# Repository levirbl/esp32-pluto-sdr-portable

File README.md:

# Portable SDR — ESP32-S3 + Pluto SDR

A handheld radio from 70 MHz to 6 GHz: spectrum and waterfall (with integrated spectrum, traces and
fine RBW), audio (AM, FM, SSB and CW) with automatic noise reduction, recording, decoders (RDS, ADS-B,
AIS, APRS, radiosondes, VOR, FPV drones), hydrogen-line radio astronomy, satellite pass prediction with Doppler correction, an RF
oscilloscope and **amateur radio transmit** on 2 m and 70 cm (test tone, WAV file in NFM, USB or
LSB, CW identification and CW messages, tracking generator, replay of IQ recordings), plus a **Tools**
app (image viewer, text editor, RF and antenna calculators, stopwatch and timer, metronome, IQ file
player and games) and a **Power saver** mode for the battery.
All of it on a 3.5" touch screen with a rotary encoder, running on a battery.

- The **Pluto SDR** is the radio: it captures the signal, computes the spectrum, demodulates the
  audio and decodes ADS-B, AIS and RDS.
- The **ESP32-S3** is the Pluto's USB host and owns the user interface: screen, touch, encoder,
  speaker and SD card. It also decodes APRS, radiosondes and VOR, and predicts satellite passes.

The device is mainly a receiver. The **Transmit** app is for **licensed radio amateurs** and only
transmits on the 2 m (144–148 MHz) and 70 cm (430–440 MHz) bands, with an on-screen confirmation and
an automatic cut-off if the ESP32 stops responding. See [Transmit](docs/apps/transmit.md).

> **Closed source.** This repository holds the ready-made binaries (ESP32 and Pluto), the SD card
> files and the documentation. The source code is not distributed.

---

## Apps

Every app has its own page with screenshots.

| App | What it does |
|---|---|
| [Everywhere](docs/apps/general.md) | Status bar, gestures, keypads, screenshots, touch lock |
| [Spectrum](docs/apps/spectrum.md) | Live spectrum and waterfall, 10 kHz to 56 MHz wide, traces, fine RBW |
| [Sweep](docs/apps/sweep.md) | Wide bands (up to 70 MHz–6 GHz) built from radio hops |
| [Search](docs/apps/search.md) | List of signals above a threshold |
| [Meter](docs/apps/meter.md) | Signal level, fox-hunt beep, RF oscilloscope |
| [Memories](docs/apps/memories.md) | Named frequencies, memory scanner, ignore list |
| [Audio](docs/apps/audio.md) | AM, NFM, WFM, USB, LSB, CW with squelch, noise reduction, EQ, zoom, Doppler |
| [Record](docs/apps/record.md) | Records the audio to WAV on the SD card |
| [Decode](docs/apps/decode.md) | RDS, ADS-B, AIS, radiosondes, APRS, VOR, satellites, FPV drones, radio astronomy |
| [Files](docs/apps/files.md) | SD card browser, WAV player and waveform viewer |
| [Tools](docs/apps/tools.md) | Images, text, calculators (RF conv, Antenna, LC), stopwatch/timer, metronome, IQ player, games |
| [Status](docs/apps/status.md) | Link, radio and device state (open it from Settings) |
| [Settings](docs/apps/settings.md) | Display, Power saver, clock, calibrations, battery, backups, firmware updates |
| [Transmit](docs/apps/transmit.md) | Amateur radio TX: tone, WAV, IQ replay, CW, tracking generator |

## Documentation

| Document | Contents |
|---|---|
| [Components](docs/COMPONENTS.md) | Parts list to build one |
| [Assembly](docs/ASSEMBLY.md) | Pinout and step-by-step assembly, with a test at each step |
| [Pluto setup](docs/PLUTO_SETUP.md) | How to prepare the Pluto so the ESP32 can talk to it |
| [Changelog](CHANGELOG.md) | What each release added and fixed |
| [Main board (PCB)](hardware/README.md) | KiCad project, Gerbers, BOM/CPL, schematic and renders of the 4-layer main board (not built yet) |

## What is in this repository

```
sdcard/              microSD card contents (copy the whole folder to the card's root)
  cfg/               settings backups and internal spur maps (written by the device)
  firmware/          ESP32 firmware for updating from the card
  pluto/             Pluto program for updating from the card
  map/mundo.map      world map for the radar views (ADS-B, AIS, APRS, radiosondes)
  rec/               audio recordings (written by the device)
  sat/               satellite orbits (TLE) and frequencies (freq.txt)
  tx/                WAV files for the Transmit app
esp32-usb/           files for the first ESP32 flash over USB
pluto/deploy/        Pluto program (rx_streaming_fft) and start-up scripts
docs/                documentation and screenshots
hardware/            main board: KiCad project, fabrication files (Gerbers, BOM, CPL), schematic and renders
```

---

## Quick start

1. **Build the hardware**: [Components](docs/COMPONENTS.md) and [Assembly](docs/ASSEMBLY.md).
2. **Set up the Pluto** (once, with the Pluto on a PC): [Pluto setup](docs/PLUTO_SETUP.md).
3. **Prepare the microSD card**: format it as FAT32 and copy the contents of `sdcard/` to its root.
4. **Flash the ESP32 over USB** the first time ([below](#first-esp32-flash-over-usb)). After that,
   updates go through the SD card.
5. **Do the first settings** on the device ([below](#first-settings-on-the-device)).

## What to add, change and remove

| Where | Add | Change | Remove |
|---|---|---|---|
| **Pluto** | `rx_streaming_fft` and `run.sh` in `/mnt/jffs2/sdr/`; `autorun.sh` in `/mnt/jffs2/` | Extended range (`ad9364`, 70 MHz–6 GHz); the USB serial line in `/etc/inittab` (`autorun.sh` redoes it at every boot); the Zynq's 2nd core is turned on by `run.sh` at every boot | The login (getty) on the USB data serial port: the SDR program takes its place |
| **ESP32-S3** | Firmware (first time over USB, then from the card) | — | — |
| **microSD card** | The `cfg`, `firmware`, `pluto`, `map`, `rec`, `sat` and `tx` folders of this repository | Orbits in `sat/` every 1–2 weeks; `sat/freq.txt` if you want other frequencies | Old firmware files in `firmware/` (optional) |
| **Assembly** | 100 Ω series resistors on the fast signals, ferrites and capacitors on each 5 V branch, clip-on ferrites on the cables | Encoder on 3V3 (never 5 V); display and card on 3V3 | Display SDO pin left unconnected; nothing on header GPIO19/20 (they are the Pluto's USB) |

## First ESP32 flash over USB

Updating from the card only works once the device already has this firmware, so the first time
goes through the cable:

1. Install **esptool** (`pip install esptool`) or use Espressif's web flasher
   (https://espressif.github.io/esptool-js/, in Chrome or Edge).
2. If the battery is connected, **open jumper JP_DEV**. Connect the PC to the devkit's **right
   USB-C** (the UART, CH343 chip). On Windows it shows up as a COM port.
3. Write the four files from `esp32-usb/`, each at its address:

```bash
esptool --chip esp32s3 --port COM12 --baud 921600 write-flash --flash-mode dio --flash-freq 80m --flash-size 16MB 0x0 bootloader.bin 0x8000 partitions.bin 0xe000 boot_app0.bin 0x10000 sdr.bin
```

Replace `COM12` with your port. In the web flasher, add the same files at the same addresses
(0x0, 0x8000, 0xe000 and 0x10000).

The board must be an **ESP32-S3-N16R8** (16 MB flash, 8 MB octal PSRAM).

## Updating the firmware from the card

1. Copy the new `.bin` to `/firmware` on the card. Use the app firmware (the one in
   `sdcard/firmware/`), never a `.merged.bin` or the `bootloader.bin`.
2. On the device, open **Settings > Firmware from card**, pick the file and confirm.
3. The ESP32 checks the whole image before switching. If something fails halfway, the current
   firmware stays. After writing, it restarts and the status bar shows that the firmware changed.
4. If you don't like the new firmware, use **Back to previous** on the same screen.

The device refuses files that are not from this project or are not an ESP32-S3 image. The date in
the list is the file's date on the card.

The Pluto program also updates from the card: copy `rx_streaming_fft` to `/pluto` and use
**Settings > Pluto from card** (details in [Pluto setup](docs/PLUTO_SETUP.md)). The first install of
a version that has this feature is still done over SSH.

## First settings on the device

Navigation: **turn** the encoder to select; **press** to enter or confirm; **hold** the button
(0.6 s) to go back to the menu; **hold 2 s** to lock and unlock the touch screen.

1. **Settings > Calibrate touch**: tap the corners shown. The factory calibration is the prototype
   panel's and may not fit yours.
2. **Location** (in the ADS-B, AIS, APRS, Radiosonde or Satellites bar): type your latitude and
   longitude in decimal degrees. South and west are negative.
3. **Settings > Date and time**: choose the time zone and an **FM station in your city that sends
   the time over RDS** (the default is 102.7 MHz, in Fortaleza). The clock then sets itself while
   you are on the home menu. You can also set it by hand.
4. **Settings > Crystal (FM station)**: pick a strong local FM station and apply the correction.
   This fixes the Pluto's frequency error.
5. **Settings > Internal spurs** (optional, recommended): **with no antenna**, record the bands you
   use most (for example FM, 2 m and 70 cm). The spurs the device makes itself disappear from the
   spectrum and the audio. Record them again whenever the assembly or the power supply changes.
6. **Settings > Backup to card**: save a copy of the settings.

## microSD card

Use FAT32. The prototype uses an 8 GB card.

| Folder | What goes there |
|---|---|
| `/firmware` | Firmware `.bin` files, for **Settings > Firmware from card** |
| `/pluto` | The Pluto program (`rx_streaming_fft`), for **Settings > Pluto from card** |
| `/map` | `mundo.map`, the world map (coastline, borders, roads, cities and airports) drawn behind the radars. Without it the radar works, just with no map |
| `/sat` | Orbits (`*.txt` or `*.tle`, 3-line TLE format) and `freq.txt` (frequencies and modes of each satellite) |
| `/cfg` | Settings backups, automatic copies and internal spur maps. Written by the device |
| `/rec` | WAV recordings (48 kHz, mono, 16-bit). Written by the device |
| `/screenshots` | PNG screenshots. Written by the device |
| `/tx` | WAV files for the Transmit app (16-bit PCM, 8–96 kHz, mono or stereo; up to 3 min per transmission) |

The `.gitkeep` files only make Git keep the empty folders and can be deleted.

**Updating the orbits**: orbits get old; after 14 days the Satellites app warns you. Download the
"Amateur Radio" and "Space Stations" groups from CelesTrak in TLE format
(https://celestrak.org/NORAD/elements/) and replace `amateur.txt` and `stations.txt` in `/sat`.
Then tap **Reload** in the Satellites app.

**`freq.txt` format**: one frequency per line, `NORAD MHz mode[/baud] name`. For example
`25544 145.8 FM ISS voice` or `25544 145.825 APRS/1200 ISS APRS`. The NORAD number is the same as in
the TLE files. The modes are FM, SSTV, APRS, AFSK, CW, USB, LSB, PSK and DADOS (data). Lines starting
with `#` are comments.

## Third-party data

- **Map** (`mundo.map`): built from [Natural Earth](https://www.naturalearthdata.com/), public
  domain.
- **Frequencies** (`freq.txt`): built from the [SatNOGS DB](https://db.satnogs.org/), license
  [CC BY-SA 4.0](https://creativecommons.org/licenses/by-sa/4.0/). `freq.txt` carries the same
  license.
- **Orbits** (`amateur.txt`, `stations.txt`): [CelesTrak](https://celestrak.org/).

## Responsible use

Listening to broadcast, amateur, aviation, maritime and satellite bands is the intended use. The
content of private communications is protected by law (in Brazil, Constitution, art. 5, XII): do
not disclose or use it. The device's decoders only handle public navigation, identification and
telemetry signals.

Transmitting requires an amateur radio license (in Brazil, from ANATEL) and is only allowed within
your license class privileges; the device's 144–148 and 430–440 MHz ranges may be wider than what
your class allows. Identify your station as the regulations require, use a proper antenna and never
connect the TX to the RX without attenuation.

## Known limitations

- The range is 70 MHz to 6 GHz. Outside 325 MHz–3.8 GHz the Pluto's chip (AD9363) works, but out
  of specification. Shortwave (HF) would need an external upconverter.
- Not yet validated on the air: APRS, radiosondes, VOR and AIS (tested on the PC; there was no
  traffic where they were tried). The IQ replay in Transmit was not measured in RF either.
- Touch calibration, crystal correction and internal spur maps depend on each unit and assembly.
- TX: power was not measured in dBm (only as relative levels on the Pluto's own receiver); the
  Pluto's nominal maximum is a few dBm. The tone's image (LO − tone) measured at least 43 dB below
  the signal on the prototype; the device still requires the image to be inside the band.
- Boost converter: the XL6009 and MT3608 that were tried cannot power the whole device (see
  [Assembly](docs/ASSEMBLY.md)); the prototype uses an external 5 V supply until it moves to a TPS61088.

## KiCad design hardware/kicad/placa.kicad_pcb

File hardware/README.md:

# Main board (PCB)

The main board of the portable SDR. It carries the battery, its charger and protection, the 5 V boost converter,
the ESP32-S3 with the display, microSD, audio and controls, and it powers the **Pluto SDR**. The Pluto stays a
separate module, mounted behind the board and connected by one short USB-C cable for both data and power.

Designed in **KiCad 10**, 4 layers, about **58 × 150 mm**, built for JLCPCB (assembly files included).

| Front (layout) | 3D |
|---|---|
|  | <br> |

Status: schematic and layout finished and checked (DRC: 0 errors, 0 unrouted; every one of the 526 pins matches the
schematic; the firmware pin map in `sdr/pins_config.h` is checked against the netlist). **Not built yet.**

## Contents

| Folder | What is in it |
|---|---|
| `kicad/` | KiCad 10 project: `placa.kicad_pro` (open this), schematic (`placa.kicad_sch` with two sheets: `energia.kicad_sch` power, `esp32.kicad_sch` ESP32 and peripherals), `placa.kicad_pcb`, design rules (`placa.kicad_dru`, JLCPCB 4-layer), project footprints/symbols (`proj.pretty`, `proj.kicad_sym`) and 3D models (`3d/`) |
| `fabrication/` | `gerbers_jlcpcb.zip` (Gerbers + drill), `bom_jlcpcb.csv` (with LCSC part numbers and quantity per board), `cpl_jlcpcb.csv` (pick and place, rotations already checked in the JLCPCB 3D preview), `lcsc_order.csv` (one line per LCSC part, quantities for one board) |
| `images/` | Renders and the schematic (`schematic.pdf`, and one SVG per sheet) |

Schematic: [power](images/schematic_power.svg) · [ESP32 and peripherals](images/schematic_esp32.svg) · [PDF](images/schematic.pdf)

## How the board works

```
USB-C J1 ──► BQ24074 charger ──► SYS ──► power switch (SW1 + P-MOS Q3) ──► TPS61088 boost ──► +5 V
                │  ▲                                                               │
                ▼  │                                                               ├─► JP2 ► ferrite ► eFuse ► USB-C J2 ► PLUTO
       battery J3 (7 A fuse,                                                       ├─► JP3 ► ferrite ► AMS1117 ► 3.3 V ► ESP32, SD, display, mic
       DW01A + 8205A protection)                                                   └─► JP4 ► ferrite ► MAX98357A ► speaker
```

1. **Battery (J3)**: one LiPo cell soldered to the two holes (+ on pin 1), through a 7 A fuse and a DW01A + 2× 8205A
   protection (over-charge, over-discharge, short circuit). A third 8205A footprint (Q4) is left unpopulated.
2. **Charging (J1, BQ24074)**: the USB-C port charges the battery (0.89 A) and powers the device at the same time
   (power path, 1.46 A input limit). Red LED = charging, green LED = on USB power; the ESP32 also reads "on USB power"
   on GPIO21.
3. **On/off (SW1)**: the slide switch turns on a P-MOS between the system rail and the boost. When off, nothing after
   it draws current.
4. **Boost (TPS61088)**: 3.0–4.2 V → 5.1 V, ~1 MHz.
5. **Three 5 V branches**, each with a solder jumper (cut it to measure the current) and its own ferrite:
   - **Pluto**: TPS259470A eFuse (2.5 A limit, UVLO 4.56 V, OVLO 5.68 V), then USB-C **J2**. The ESP32 is the USB host:
     the same cable carries 5 V and USB data. J2 has 56 kΩ pull-ups on CC (source) and USBLC6 ESD protection.
   - **ESP32**: AMS1117 → 3.3 V for the ESP32-S3-WROOM-1U, microSD, display and microphone.
   - **Audio**: MAX98357A class-D amplifier → JST-PH speaker connector.
6. **Programming**: the same USB-C J1 goes to a CH340C (own 3.3 V regulator) with auto-reset, so the ESP32 is
   flashed without pressing BOOT. BOOT and RESET buttons are on the board anyway.
7. **Battery voltage**: 300 k / 100 k divider to GPIO1 (same as the firmware's `BAT_DIV = 4`).

### Board map

| Area | Parts |
|---|---|
| Top edge | Display socket J101 (14 pins, 3.5" ILI9488 module) |
| Top | ESP32-S3-WROOM-1U (U.FL connector for an external antenna), microSD J102, microphone ICS-43434 (sound hole in the PCB) |
| Top right | USB-C **J2 to the Pluto**, eFuse, ESD; the cut-out under J2 leaves room for the cable plug |
| Middle | 3.3 V regulator, CH340C + auto-reset, encoder pull-ups, test points |
| Left edge | USB-C **J1** (charge and program) |
| Middle | Charger, battery holes J3, fuse, protection, power switch MOSFET, boost (inductor and output caps), branch jumpers and ferrites |
| Bottom | Rotary encoder, MAX98357A + speaker connector, BOOT/RESET, LEDs, power switch SW1, PTT (J104) and expansion (J106, GPIO 38/48) headers |

### Solder jumpers

| Jumper | Default | Use |
|---|---|---|
| JP2 / JP3 / JP4 | closed | Cut to measure the current of the Pluto / ESP32 / audio branch |
| JP1 | open | Close to force the boost into fixed PWM |
| JP101 / JP102 | JP101 closed | Display supply: 3.3 V (default) or 5 V (cut JP101, bridge JP102) |
| JP103 | closed | CH340C at 3.3 V (leave it) |

Test points: TP1 VBUS, TP2 SYS, TP3 battery after the fuse, TP4 boost input, TP5 +5 V, TP6 Pluto 5 V, TP7 Pluto VBUS
(after the eFuse), TP8 3.3 V, TP9/TP10 GND, TP11 battery-sense pin. Bring-up order: USB only (TP1, TP2, green LED) →
battery and switch (TP5 ≈ 5.1 V) → TP8 3.3 V and flash the ESP32 → connect the Pluto last.

## Designed for low RF noise

This board replaces a breadboard/perfboard build in which most of the receiver's problems were noise made by the
device itself (display SPI edges, the audio amplifier, the boost, currents on the cables). The layout addresses each
of them:

- **4 layers with a solid ground plane** (layer 2, 92 % of the board in one piece) right under every top-layer signal,
  so return currents stay short and under their traces.
- **Ground pour on the top and bottom layers**, stitched to the inner plane with ~200 vias every ~3.5 mm: no floating
  copper, a closed "box" around the signals.
- **Separate filtered 5 V branches**: Pluto, ESP32 and audio each have a ferrite bead and local capacitors, so the
  switching noise of one load does not reach the others; the Pluto branch also has an eFuse.
- **100 Ω series resistors at the ESP32** on display SCK/MOSI, microSD SCK/MOSI and I2S BCLK/LRCK/DOUT, which slow the
  edges that used to show up as spurs and a "robotic" sound in FM (measured on the prototype).
- **Speaker outputs filtered** with a ferrite and a capacitor to ground on each line (MAX98357A EMI filter); on the
  prototype the amplifier was the largest single noise source.
- **Compact boost layout**: input caps, inductor, IC and output caps close together on a copper area, with thermal vias,
  to keep the high-current switching loop small.
- **Wide power paths**: the Pluto branch is 1 mm wide end to end (plus copper areas and 4 vias from the plane);
  the battery, system and boost paths run on copper areas.
- **USB data** routed as pairs over the ground plane, with ESD protection at both USB-C connectors.
- Decoupling capacitors within ~3.5 mm of every IC supply pin.
- External antenna connector on the ESP32 module (WROOM-1U) instead of a PCB antenna.

## Component changes from the prototype

The prototype used ready-made modules on a perfboard. On this board they became parts soldered on the PCB, and some
were replaced:

| Prototype | On this board | Why |
|---|---|---|
| ESP32-S3 DevKitC-1 (N16R8) | ESP32-S3-WROOM-1U-N16R8 module | Same chip and memory, much smaller, external antenna (U.FL) |
| USB on the DevKit | CH340C + auto-reset on the charge USB-C | Program and charge through one port |
| TP4056 charger module | **BQ24074** | Power path (runs from USB while charging), current limits set by resistors, charge/power LEDs |
| XL6009 boost, then MT3608 | **TPS61088** | The XL6009 did not start under load from a single cell; the MT3608 reset the device under the Pluto's load. The TPS61088 (already tested on a module) holds the whole device |
| DW01A + FS8205A (TP4056 module) | DW01A + 2× 8205A (HXY), 3rd optional | FS8205A discontinued at LCSC; two in parallel for less loss |
| Direct 5 V wire to the Pluto | **TPS259470A eFuse** + USB-C source port | Short-circuit and over/under-voltage protection for the Pluto; the TPS259472A had no stock |
| — | CSD25402Q3A P-MOS + slide switch | Real on/off switch (the AON6411 is not available at JLCPCB) |
| MAX98357 module | MAX98357A chip | On the board, with the EMI output filter |
| INMP441 microphone module | **ICS-43434** soldered on the board | INMP441 out of stock; same I2S interface |
| microSD module | Molex 104031-0811 socket | On the board, 3.3 V only |
| KY-040 encoder module | **Bourns PEC11R-4015F-S0024** | One pulse per detent, as the firmware expects; mounts on the board |
| Jumper wires to the display | 14-pin socket | Display plugs directly on the board |

## Ordering

- PCB: upload `fabrication/gerbers_jlcpcb.zip` (4 layers, 1.6 mm).
- Assembly at JLCPCB: `bom_jlcpcb.csv` + `cpl_jlcpcb.csv`. The encoder SW103 is through-hole and is not in the CPL
  (JLCPCB warns about it; continue and solder it by hand). Unpopulated on purpose: Q4, C12, C116–C118, R111, R121,
  J104, J106.
- Hand assembly: order the PCB with a top stencil and the parts from `lcsc_order.csv`. The QFN parts (BQ24074,
  TPS61088, TPS259470A, MAX98357A), the ICS-43434 microphone, the CSD25402 and the ESP32 ground pad need hot air or a
  hot plate; the rest can be done with an iron.
- Hand-soldered parts in any case: encoder SW103, 1×14 female header for the display (J101), battery wires (J3).

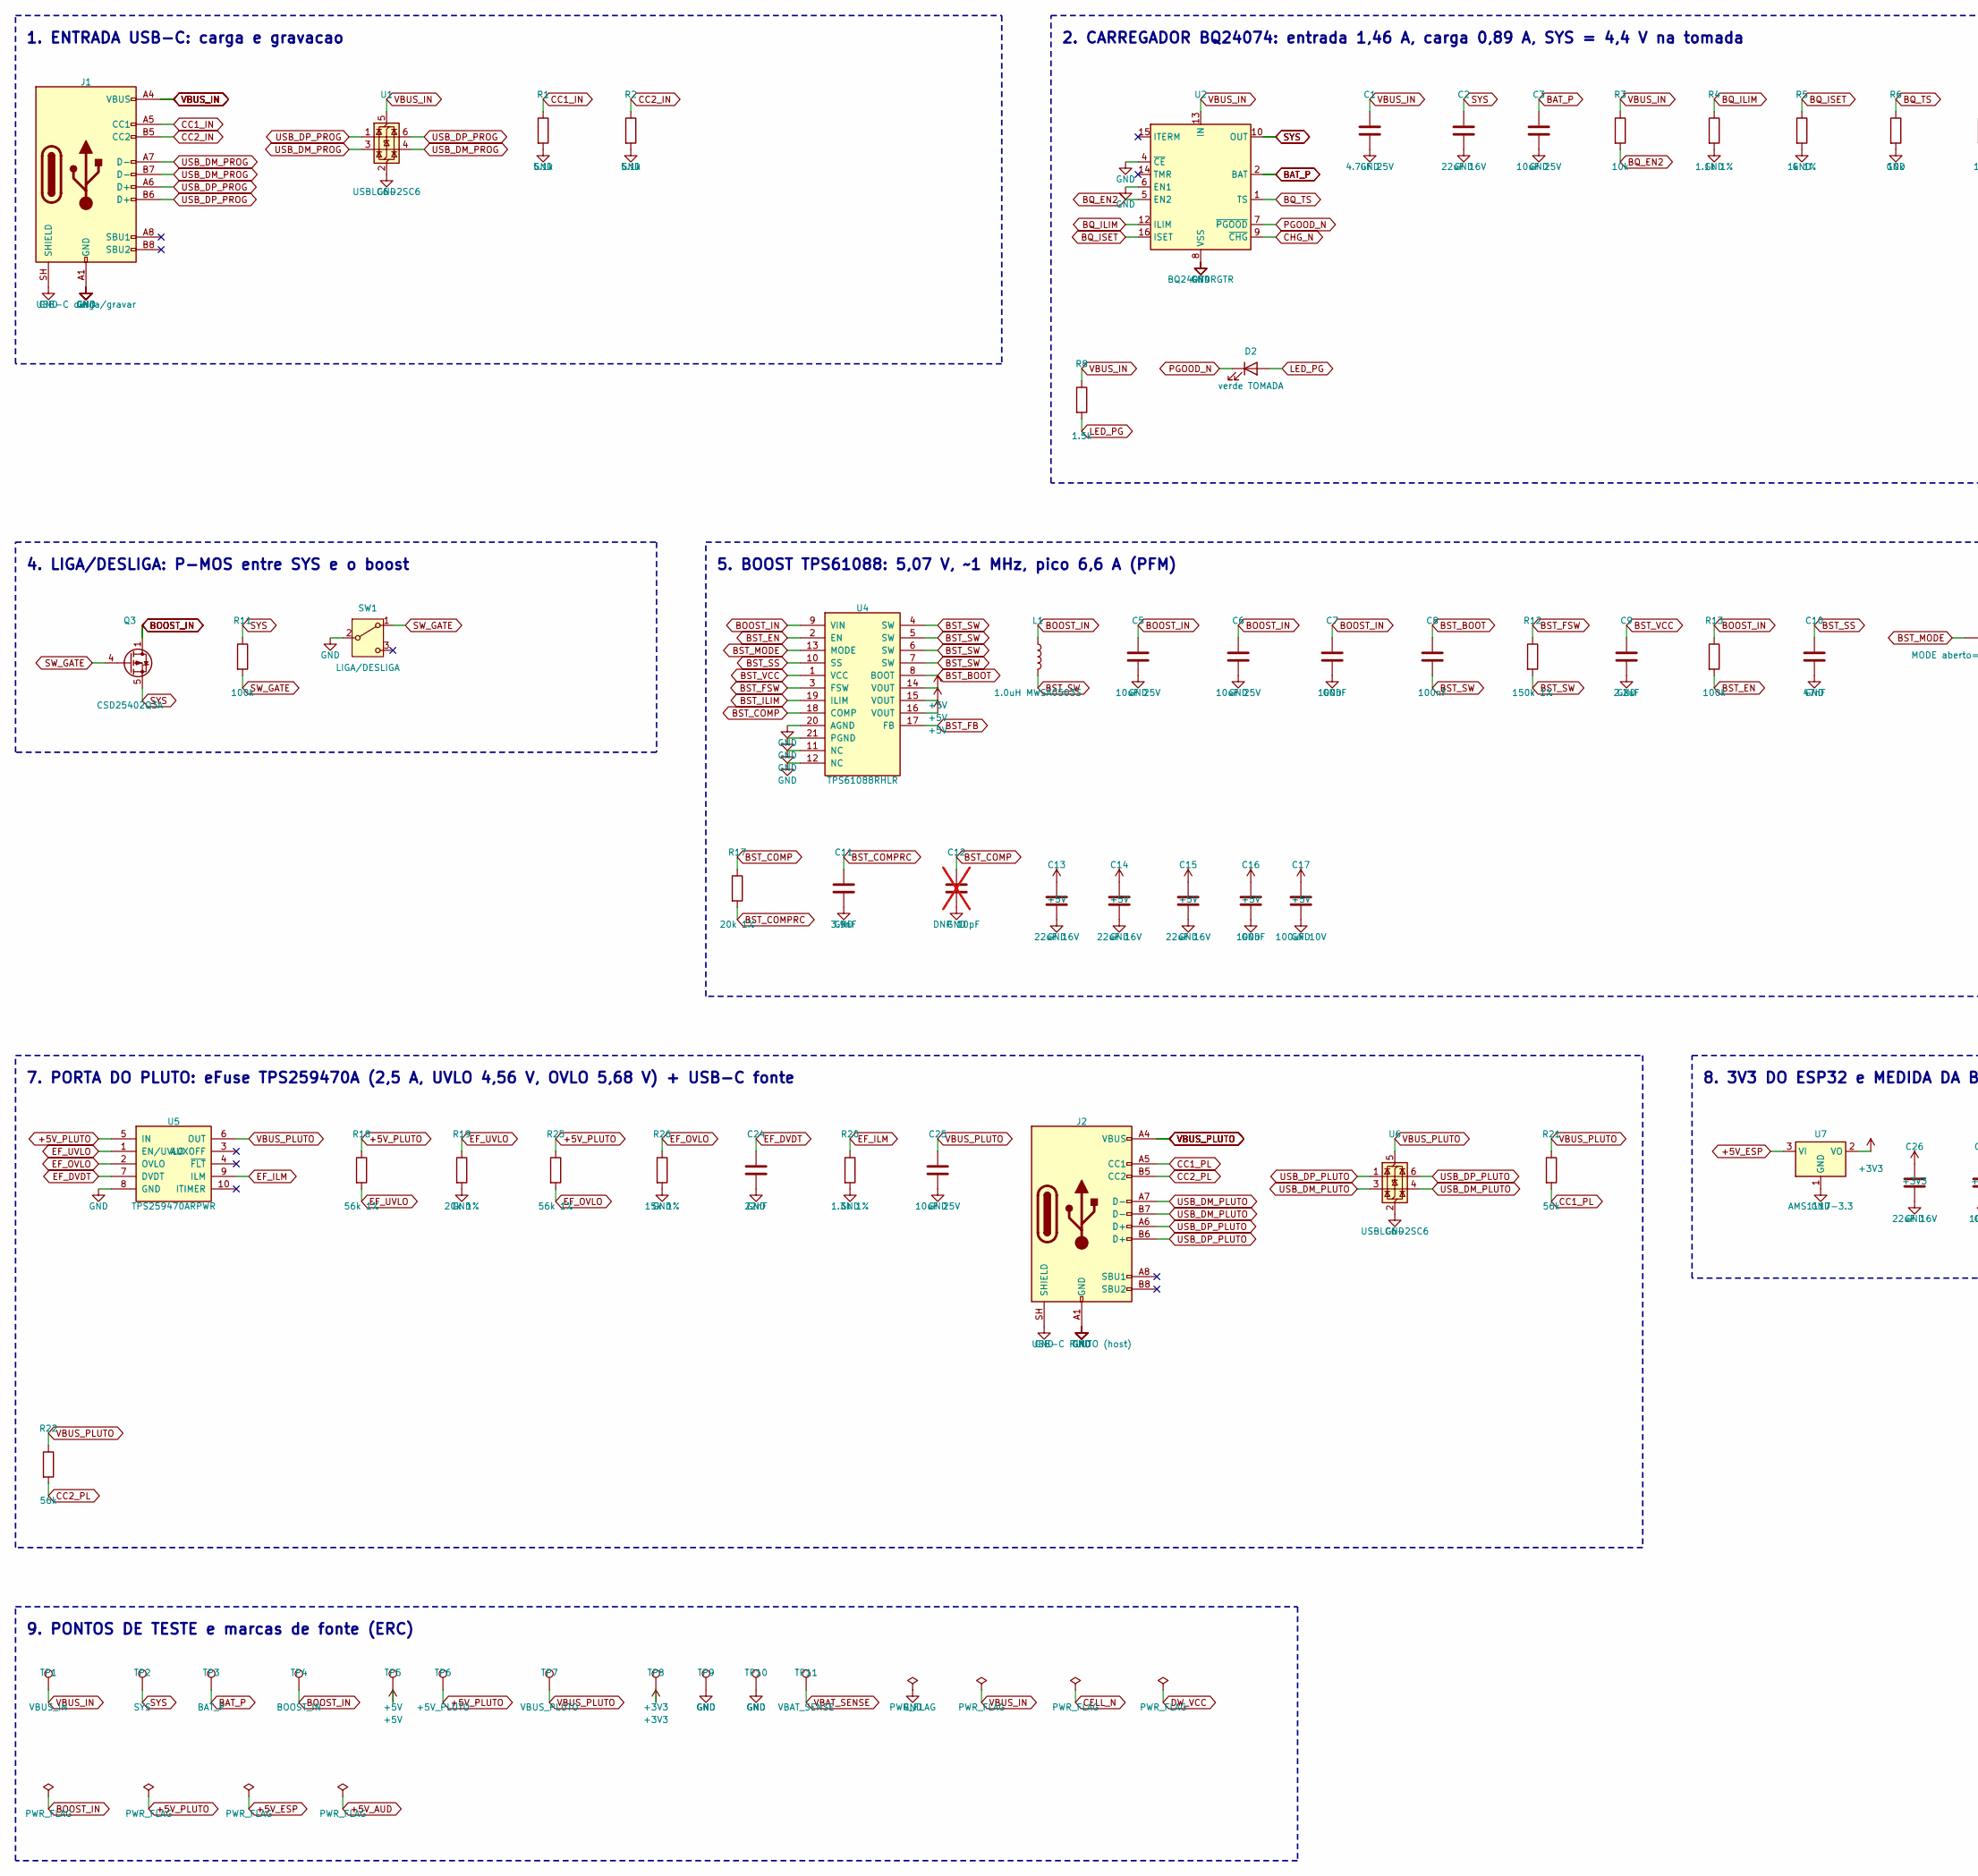
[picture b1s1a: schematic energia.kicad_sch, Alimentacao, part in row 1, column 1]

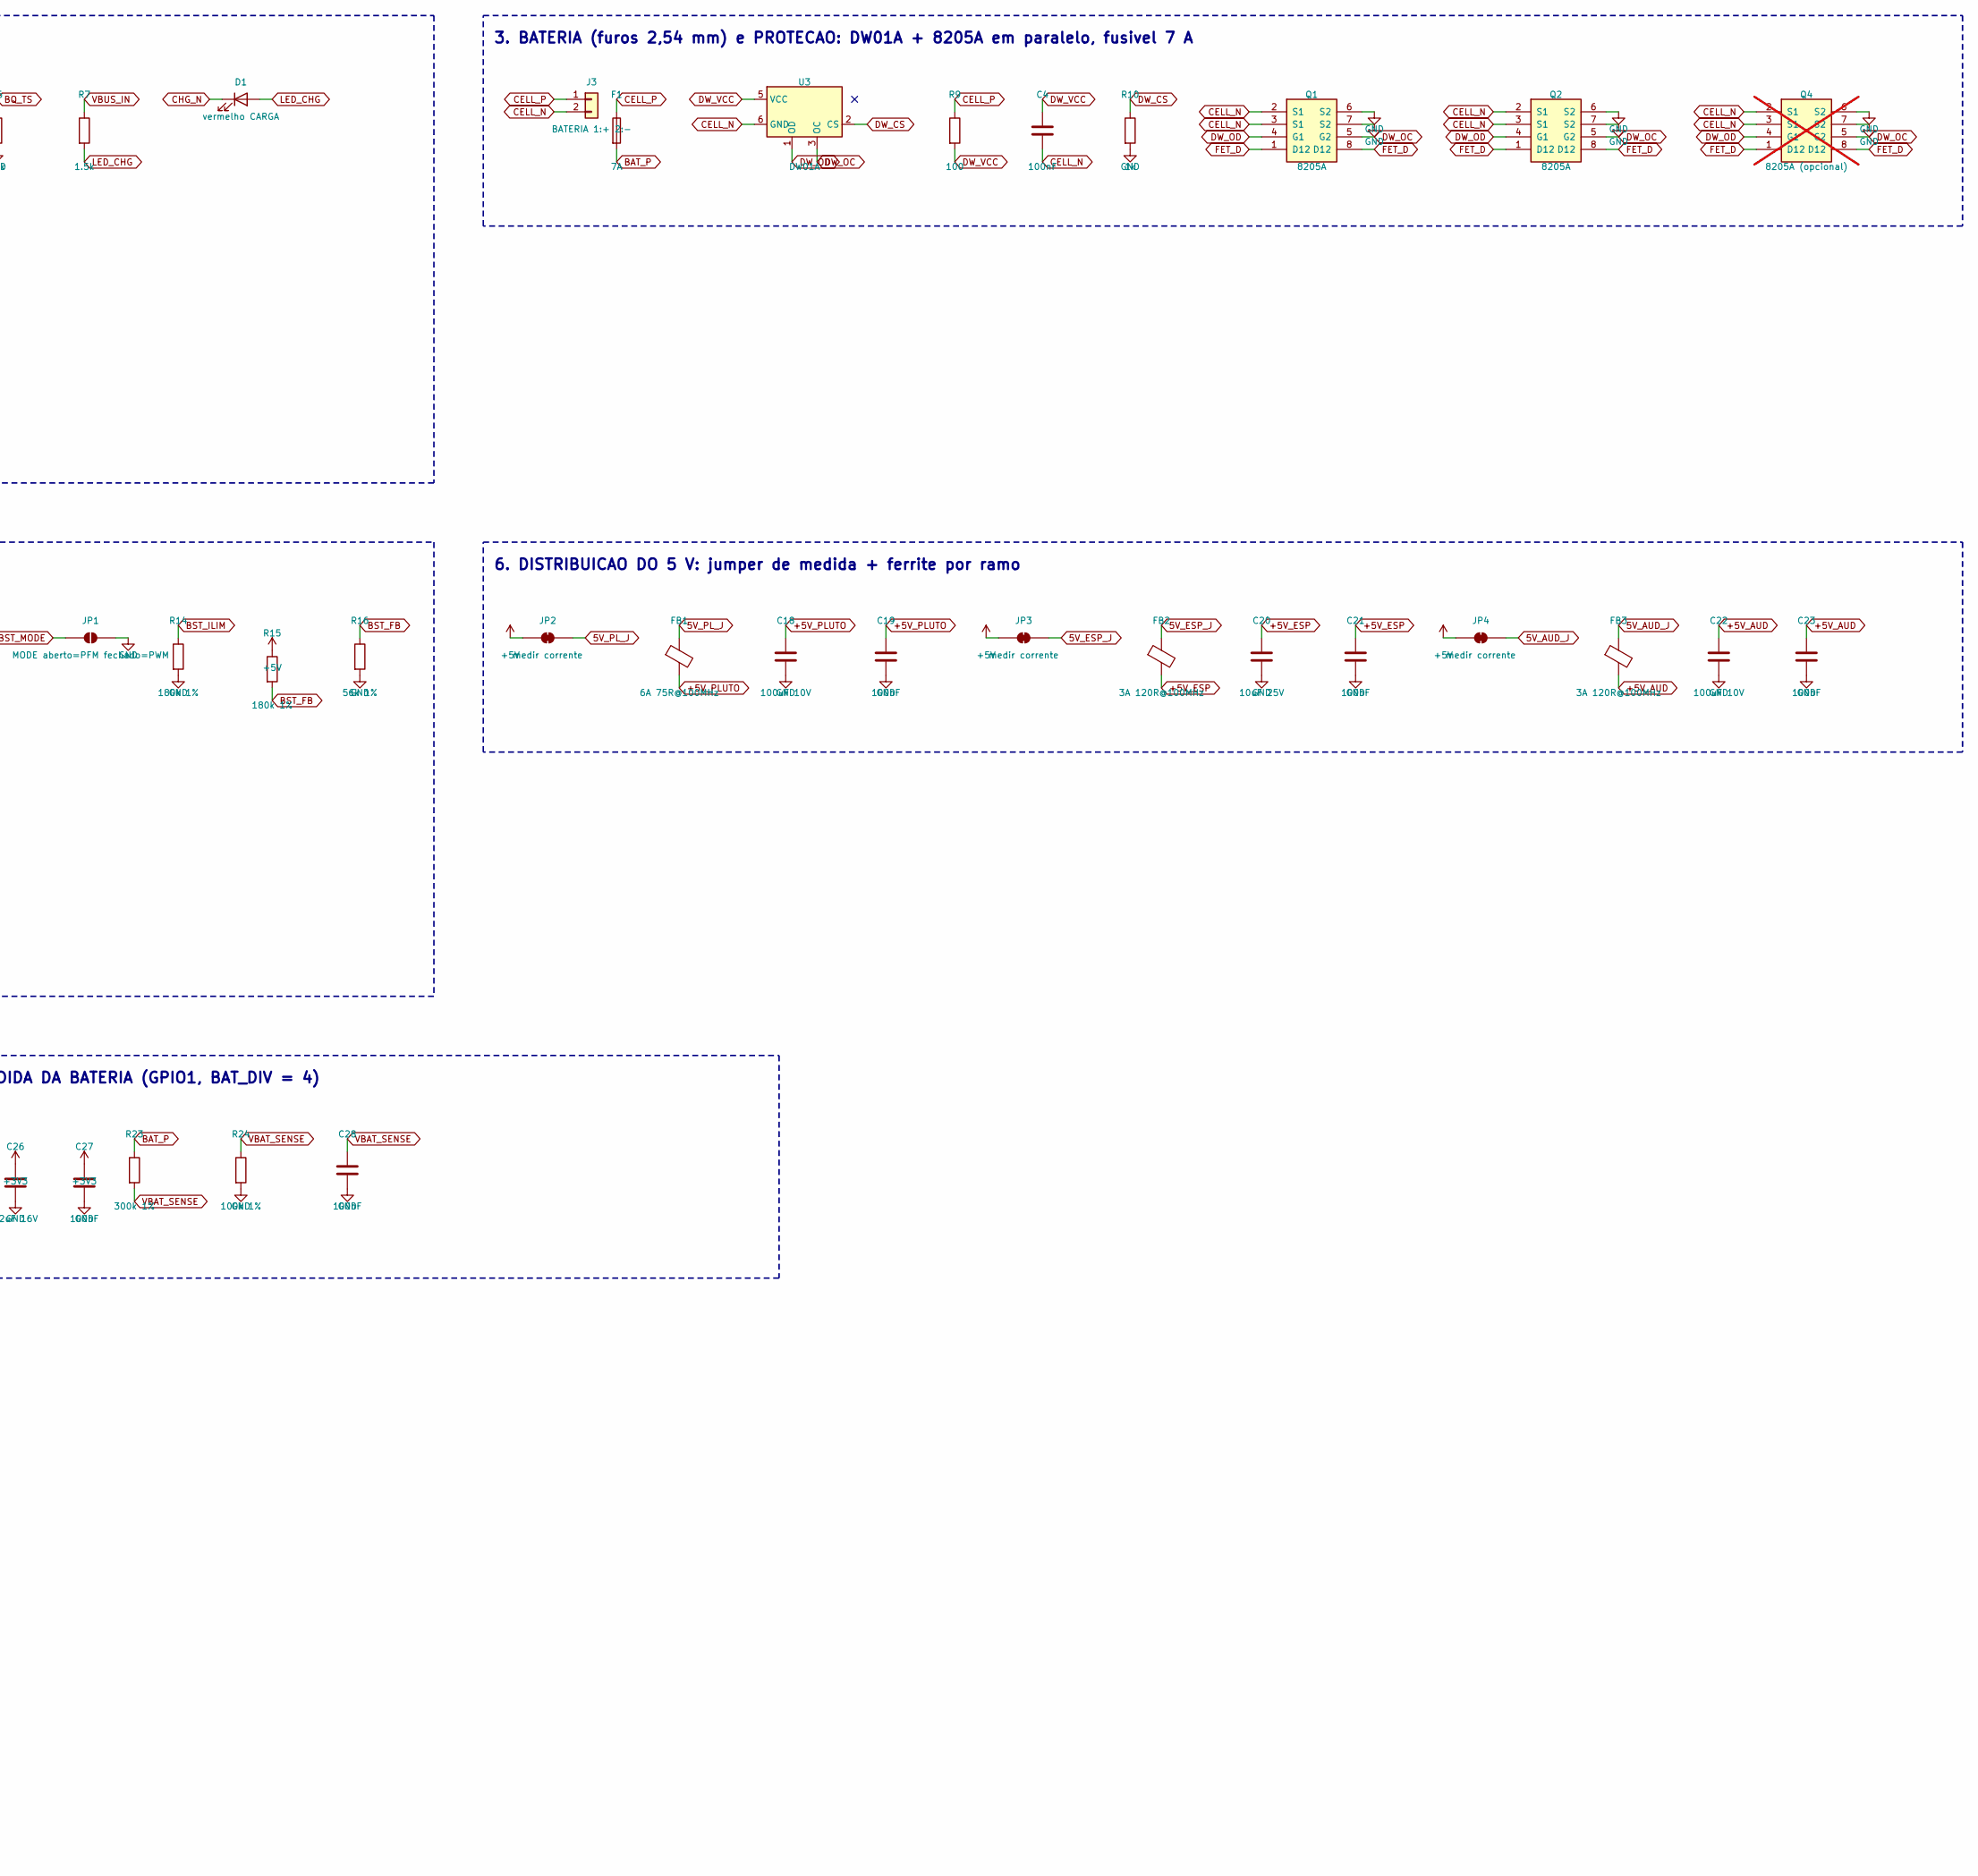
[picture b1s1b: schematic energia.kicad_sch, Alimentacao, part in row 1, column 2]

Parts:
C1: 4.7uF 25V; C_0805_2012Metric; LCSC C1779
C2, C13, C14, C15, C26: 22uF 16V; C_1206_3216Metric; LCSC C90146
C3, C5, C6, C20, C25: 10uF 25V; C_0805_2012Metric; LCSC C15850
C4, C7, C8, C16, C19, C21, C23, C27, C28: 100nF; C_0603_1608Metric; LCSC C14663
C9: 2.2uF; C_0603_1608Metric; LCSC C23630
C10: 47nF; C_0603_1608Metric; LCSC C1622
C11: 3.9nF; C_0603_1608Metric; LCSC C309474
C12: DNP 10pF; C_0603_1608Metric; LCSC C1634; not fitted
C17, C18, C22: 100uF 10V; C_1210_3225Metric; LCSC C23742
C24: 22nF; C_0603_1608Metric; LCSC C21122
D1: vermelho CARGA; LED_0603_1608Metric; LCSC C2286
D2: verde TOMADA; LED_0603_1608Metric; LCSC C12624
F1: 7A; Fuse_1206_3216Metric; LCSC C183154
FB1: 6A 75R@100MHz; L_1206_3216Metric; LCSC C2661688
FB2, FB3: 3A 120R@100MHz; L_1206_3216Metric; LCSC C139197
J1: USB-C carga/gravar; USB_C_Receptacle_HRO_TYPE-C-31-M-12; LCSC C165948
J2: USB-C PLUTO (host); USB_C_Receptacle_HRO_TYPE-C-31-M-12; LCSC C165948
J3: BATERIA 1:+ 2:-; PinHeader_1x02_P2.54mm_Vertical
JP1: MODE aberto=PFM fechado=PWM; SolderJumper-2_P1.3mm_Open_RoundedPad1.0x1.5mm
JP2, JP3, JP4: medir corrente; SolderJumper-2_P1.3mm_Bridged2Bar_RoundedPad1.0x1.5mm
L1: 1.0uH MWSA0503S; L_Sunlord_MWSA0503S; LCSC C408355
Q1, Q2: 8205A; TSSOP-8_4.4x3mm_P0.65mm; LCSC C5148694
Q3: CSD25402Q3A; VSON-8_3.3x3.3mm_P0.65mm_NexFET; LCSC C111356
Q4: 8205A (opcional); TSSOP-8_4.4x3mm_P0.65mm; LCSC C5148694; not fitted
R1, R2: 5.1k; R_0603_1608Metric; LCSC C23186
R3, R6: 10k; R_0603_1608Metric; LCSC C25804
R4: 1.1k 1%; R_0603_1608Metric; LCSC C137780
R5: 1k 1%; R_0603_1608Metric; LCSC C21190
R7, R8: 1.5k; R_0603_1608Metric; LCSC C22843
R9: 100; R_0603_1608Metric; LCSC C22775
R10: 1k; R_0603_1608Metric; LCSC C21190
R11, R13: 100k; R_0603_1608Metric; LCSC C25803
R12: 150k 1%; R_0603_1608Metric; LCSC C22807
R14, R15: 180k 1%; R_0603_1608Metric; LCSC C22827
R16, R18, R25: 56k 1%; R_0603_1608Metric; LCSC C23206
R17, R19: 20k 1%; R_0603_1608Metric; LCSC C4184
R20: 1.3k 1%; R_0603_1608Metric; LCSC C22767
R21, R22: 56k; R_0603_1608Metric; LCSC C23206
R23: 300k 1%; R_0603_1608Metric; LCSC C23024
R24: 100k 1%; R_0603_1608Metric; LCSC C25803
R26: 15k 1%; R_0603_1608Metric; LCSC C22809
SW1: LIGA/DESLIGA; SW_SPDT_PCM12; LCSC C221841
TP1: VBUS_IN; TestPoint_Pad_D1.5mm
TP2: SYS; TestPoint_Pad_D1.5mm
TP3: BAT_P; TestPoint_Pad_D1.5mm
TP4: BOOST_IN; TestPoint_Pad_D1.5mm
TP5: +5V; TestPoint_Pad_D1.5mm
TP6: +5V_PLUTO; TestPoint_Pad_D1.5mm
TP7: VBUS_PLUTO; TestPoint_Pad_D1.5mm
TP8: +3V3; TestPoint_Pad_D1.5mm
TP9, TP10: GND; TestPoint_Pad_D1.5mm
TP11: VBAT_SENSE; TestPoint_Pad_D1.5mm
U1, U6: USBLC6-2SC6; SOT-23-6; LCSC C2969755
U2: BQ24074RGTR; VQFN-16-1EP_3x3mm_P0.5mm_EP1.6x1.6mm_ThermalVias; LCSC C54313
U3: DW01A; SOT-23-6; LCSC C42380662
U4: TPS61088RHLR; Texas_VQFN-RHL-20_ThermalVias; LCSC C87357
U5: TPS259470ARPWR; TI_RPW0010A; LCSC C3662799
U7: AMS1117-3.3; SOT-223-3_TabPin2; LCSC C6186

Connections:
5V_AUD_J: FB3.1, JP4.2 (B)
5V_ESP_J: FB2.1, JP3.2 (B)
5V_PL_J: FB1.1, JP2.2 (B)
+3V3: C26.1, C27.1, TP8.1, U7.2 (VO); also elsewhere on the board
+5V: C13.1, C14.1, C15.1, C16.1, C17.1, JP2.1 (A), JP3.1 (A), JP4.1 (A), R15.1, TP5.1, U4.14 (VOUT), U4.15 (VOUT), U4.16 (VOUT)
+5V_AUD: C22.1, C23.1, FB3.2; also elsewhere on the board
+5V_ESP: C20.1, C21.1, FB2.2, U7.3 (VI); also elsewhere on the board
+5V_PLUTO: C18.1, C19.1, FB1.2, R18.1, R25.1, TP6.1, U5.5 (IN)
BAT_P: C3.1, F1.2, R23.1, TP3.1, U2.2 (BAT), U2.3 (BAT)
BOOST_IN: C5.1, C6.1, C7.1, L1.1, Q3.1 (D), Q3.2 (D), Q3.3 (D), R13.1, TP4.1, U4.9 (VIN)
BQ_EN2: R3.2, U2.5 (EN2)
BQ_ILIM: R4.1, U2.12 (ILIM)
BQ_ISET: R5.1, U2.16 (ISET)
BQ_TS: R6.1, U2.1 (TS)
BST_BOOT: C8.1, U4.8 (BOOT)
BST_COMP: C12.1, R17.1, U4.18 (COMP)
BST_COMPRC: C11.1, R17.2
BST_EN: R13.2, U4.2 (EN)
BST_FB: R15.2, R16.1, U4.17 (FB)
BST_FSW: R12.1, U4.3 (FSW)
BST_ILIM: R14.1, U4.19 (ILIM)
BST_MODE: JP1.1 (A), U4.13 (MODE)
BST_SS: C10.1, U4.10 (SS)
BST_SW: C8.2, L1.2, R12.2, U4.4 (SW), U4.5 (SW), U4.6 (SW), U4.7 (SW)
BST_VCC: C9.1, U4.1 (VCC)
CC1_IN: J1.A5 (CC1), R1.1
CC1_PL: J2.A5 (CC1), R21.2
CC2_IN: J1.B5 (CC2), R2.1
CC2_PL: J2.B5 (CC2), R22.2
CELL_N: C4.2, J3.2, Q1.2 (S1), Q1.3 (S1), Q2.2 (S1), Q2.3 (S1), Q4.2 (S1), Q4.3 (S1), U3.6 (GND)
CELL_P: F1.1, J3.1, R9.1
CHG_N: D1.1 (K), U2.9 (~CHG)
DW_CS: R10.1, U3.2 (CS)
DW_OC: Q1.5 (G2), Q2.5 (G2), Q4.5 (G2), U3.3 (OC)
DW_OD: Q1.4 (G1), Q2.4 (G1), Q4.4 (G1), U3.1 (OD)
DW_VCC: C4.1, R9.2, U3.5 (VCC)
EF_DVDT: C24.1, U5.7 (DVDT)
EF_ILM: R20.1, U5.9 (ILM)
EF_OVLO: R25.2, R26.1, U5.2 (OVLO)
EF_UVLO: R18.2, R19.1, U5.1 (EN/UVLO)
FET_D: Q1.1 (D12), Q1.8 (D12), Q2.1 (D12), Q2.8 (D12), Q4.1 (D12), Q4.8 (D12)
GND: C1.2, C2.2, C3.2, C5.2, C6.2, C7.2, C9.2, C10.2, C11.2, C12.2, C13.2, C14.2, C15.2, C16.2, C17.2, C18.2, C19.2, C20.2, C21.2, C22.2, C23.2, C24.2, C25.2, C26.2, C27.2, C28.2, J1.A1 (GND), J1.A12 (GND), J1.B1 (GND), J1.B12 (GND), J1.SH (SHIELD), J2.A1 (GND), J2.A12 (GND), J2.B1 (GND), J2.B12 (GND), J2.SH (SHIELD), JP1.2 (B), Q1.6 (S2), Q1.7 (S2), Q2.6 (S2), Q2.7 (S2), Q4.6 (S2), Q4.7 (S2), R1.2, R2.2, R4.2, R5.2, R6.2, R10.2, R14.2, R16.2, R19.2, R20.2, R24.2, R26.2, SW1.2 (B), TP9.1, TP10.1, U1.2 (GND), U2.4 (~CE), U2.6 (EN1), U2.8 (VSS), U2.17 (VSS), U4.11 (NC), U4.12 (NC), U4.20 (AGND), U4.21 (PGND), U5.8 (GND), U6.2 (GND), U7.1 (GND); also elsewhere on the board
LED_CHG: D1.2 (A), R7.2
LED_PG: D2.2 (A), R8.2
PGOOD_N: D2.1 (K), U2.7 (~PGOOD); also elsewhere on the board
SW_GATE: Q3.4 (G), R11.2, SW1.1 (A)
SYS: C2.1, Q3.5 (S), R11.1, TP2.1, U2.10 (OUT), U2.11 (OUT)
USB_DM_PLUTO: J2.A7 (D-), J2.B7 (D-), U6.3 (I/O2), U6.4 (I/O2); also elsewhere on the board
USB_DM_PROG: J1.A7 (D-), J1.B7 (D-), U1.3 (I/O2), U1.4 (I/O2); also elsewhere on the board
USB_DP_PLUTO: J2.A6 (D+), J2.B6 (D+), U6.1 (I/O1), U6.6 (I/O1); also elsewhere on the board
USB_DP_PROG: J1.A6 (D+), J1.B6 (D+), U1.1 (I/O1), U1.6 (I/O1); also elsewhere on the board
VBAT_SENSE: C28.1, R23.2, R24.1, TP11.1; also elsewhere on the board
VBUS_IN: C1.1, J1.A4 (VBUS), J1.A9 (VBUS), J1.B4 (VBUS), J1.B9 (VBUS), R3.1, R7.1, R8.1, TP1.1, U1.5 (VBUS), U2.13 (IN); also elsewhere on the board
VBUS_PLUTO: C25.1, J2.A4 (VBUS), J2.A9 (VBUS), J2.B4 (VBUS), J2.B9 (VBUS), R21.1, R22.1, TP7.1, U5.6 (OUT), U6.5 (VBUS)

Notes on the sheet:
1. ENTRADA USB-C: carga e gravacao
2. CARREGADOR BQ24074: entrada 1,46 A, carga 0,89 A, SYS = 4,4 V na tomada
3. BATERIA (furos 2,54 mm) e PROTECAO: DW01A + 8205A em paralelo, fusivel 7 A
4. LIGA/DESLIGA: P-MOS entre SYS e o boost
5. BOOST TPS61088: 5,07 V, ~1 MHz, pico 6,6 A (PFM)
6. DISTRIBUICAO DO 5 V: jumper de medida + ferrite por ramo
7. PORTA DO PLUTO: eFuse TPS259470A (2,5 A, UVLO 4,56 V, OVLO 5,68 V) + USB-C fonte
8. 3V3 DO ESP32 e MEDIDA DA BATERIA (GPIO1, BAT_DIV = 4)
9. PONTOS DE TESTE e marcas de fonte (ERC)
